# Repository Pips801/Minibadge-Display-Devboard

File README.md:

# Minibadge Display Devboard
A small PCB that allows you to create your own Minibadge displays!

This board provides everything your custom Minibadge display will need, including LiPo battery charging/use and USB-C power. It can be attached board-to-board with your own PCB designs, or it can be wired up using push-in WAGO wire terminals to your existing displays.

## Datasheets
* Voltage regulator - TLV62585RWT - https://www.ti.com/lit/ds/symlink/tlv62585.pdf
* Battery management system - BQ21040 - https://www.ti.com/lit/ds/symlink/bq21040.pdf
* Clock generator - 74HC4060 - https://assets.nexperia.com/documents/data-sheet/74HC_HCT4060.pdf
* Clock driver - DRV8837C - https://www.ti.com/lit/ds/symlink/drv8837c.pdf
* Powepath MUX - TPS2121 - https://www.ti.com/lit/ds/symlink/tps2121.pdf

# Specifications
* Provides your Minibadges battery or USB-C power, 3.3v@3A, CLK, GND, and VBATT.
* Supports LiPo batteries, optionally with NTC temp sensors.
  * 2x LiPo batteries of matching composition, mAh, and charge state can be wired in parallel.
  * 800mA battery charging.
* Features castellated edge-mount pads for direct board to board connections.
* Features WAGO PCB terminal blocks for custom wiring.
* Power switch disconnects minibadges while still powering the battery charging circuit.
* Solderable jumper for disabling temp sensor and selecting CLK speed.

# Limitations
* Input (USB-C): 5V@3A
* Input (Battery): 4.2V@3A
* Battery charging: 4.2V@800mA
* Output (3.3V): 3.3V@3A
* Output (CLK): 3.3V@3A
* Output (SYS): Input voltage@amperage (whichever is higher)
* Max total minibadges: 30-50

# Revisions

R2 Update list
* Better thermal management for voltage regulators under load.
* Updated PMIC ORing power path chip, replacing dual ORing diodes.
* Updated PFET for power on/off switching and system load capacity.
* Better thermal management for PFET under load.
* Improved current flow and reduced waste heat for CLK driver.
* Thicker power traces for 3.3v regulators and Battery.
* Updated silkscreen component markers.
* Updated solder paste for stronger on/off switch mounting.

R3 Update list
* Larger castellated pads for better connection.
* Addition of a second row of pads for pins.
* Swap from 3x LDO regulators to 1x Buck regulator.
* Decreased waste heat and better thermal management.
* Shrunk board height by 2.54mm.
* Added technical limitations on silkscreen.

# Designing a Minibadge display
### Setup
* Import Minibadge footprints and symbols into KiCad.
* Import DevBoard footprint and symbol into KiCad.

### Schematic
* Create schematic with as many minibadges as you want.
* Import the Devboard symbol and wire up CLK, GND, and SYS (VBATT/5V).
* Wire up the minibadges 3.3v lines.

### PCB
* Arrange all of your minibadges.
* Finalize your board shape.
* Place the Devboard on the back of the PCB with the USB port against the edge of your board.
* Wire up your CLK, GND, 3x 3.3v, and SYS (VBATT/5V)

# Assembly
1. Solder the `SPEED` jumper to select the Clock frequency. F for Fast, S for Slow.
2. Solder or attach (through the WAGO) your battery positive and negative leads.
3. If your battery has an NTC temperature wire (third wire, usually white or yellow) connect it to the NTC pad or terminal. Solder the `NTC` jumper to `Y` (Yes NTC)
4. If your battery does not have an NTC temperature wire, solder the `NTC` jumper to the `N` (No NTC) position.
5. Solder or wire up your 3 different 3.3v lines from your display board.
6. Solder or wire up GND, SYS (VBATT/5V), and CLK to the appropriate connections on your display.

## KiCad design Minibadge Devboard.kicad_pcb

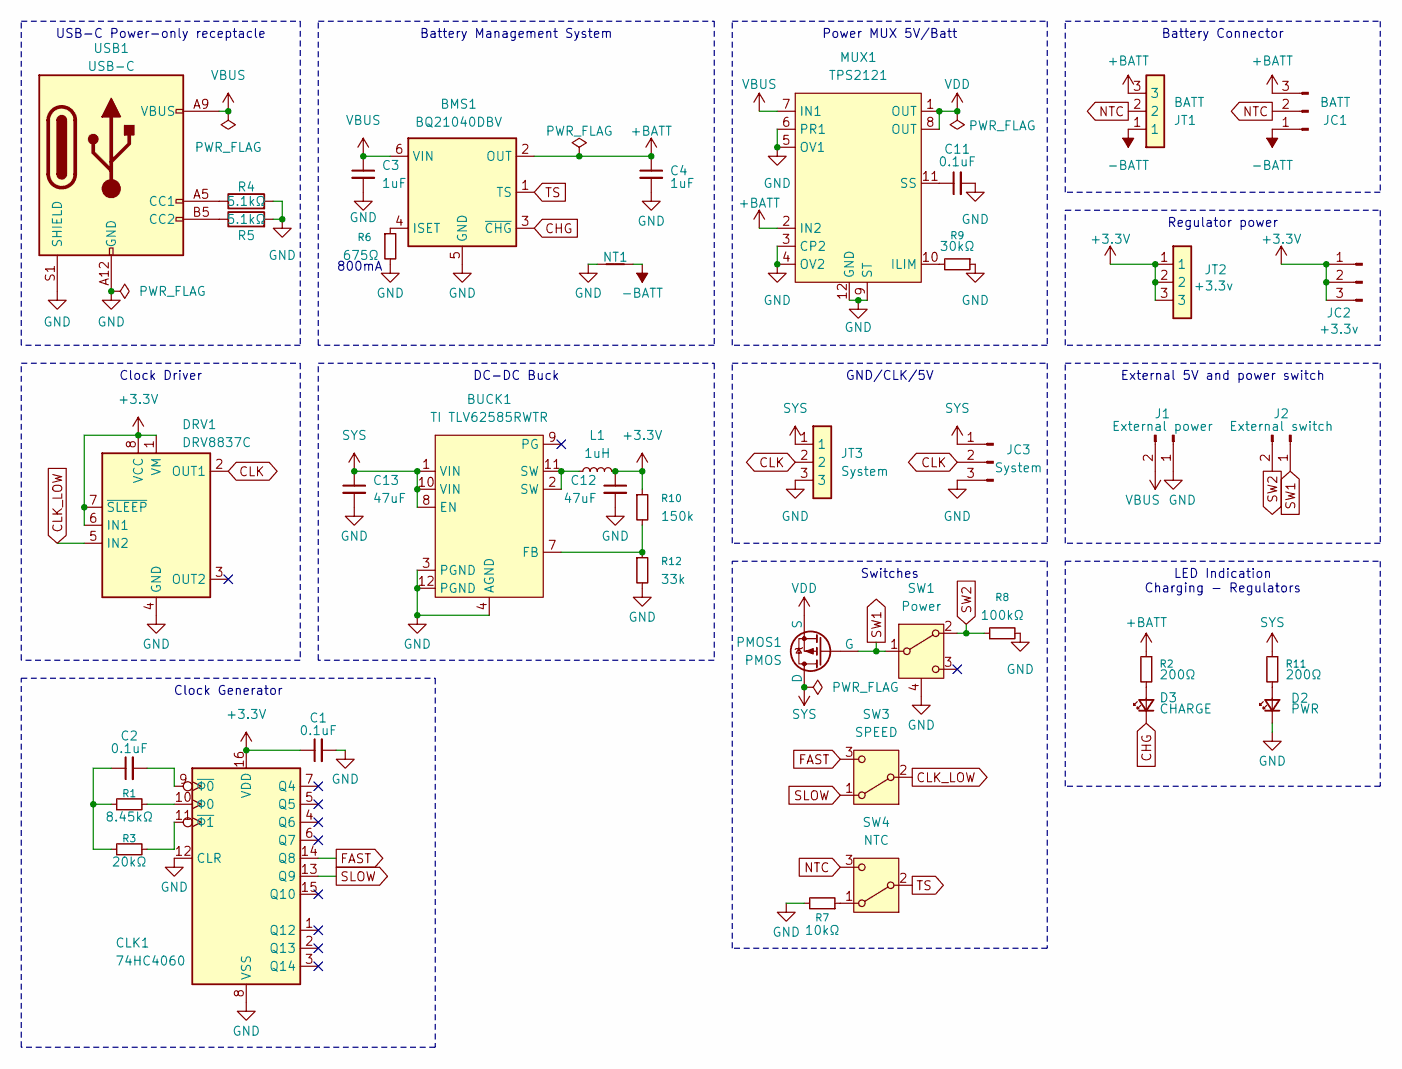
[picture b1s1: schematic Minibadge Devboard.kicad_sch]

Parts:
BMS1: BQ21040DBV; SOT-23-6; LCSC Part # C202311
BUCK1: TI TLV62585RWTR; TLV62585RWTR; LCSC Part # C406872
C1, C2, C11: 0.1uF; C_0603_1608Metric; LCSC Part # C14663
C3, C4: 1uF; C_0603_1608Metric; LCSC Part # C15849
C12, C13: 47uF; C_1206_3216Metric; LCSC Part # C96123
CLK1: 74HC4060; TSSOP-16-1EP_4.4x5mm_P0.65mm; LCSC Part # C354054
D2: PWR; LED_0603_1608Metric; LCSC Part # C2286
D3: CHARGE; LED_0603_1608Metric; LCSC Part # C2286
DRV1: DRV8837C; WSON-8-1EP_2x2mm_P0.5mm_EP0.9x1.6mm; LCSC Part # C191000
J1: External power; Castellated pins 1x02
J2: External switch; Castellated pins 1x02
JC1: BATT; Castellated pins 1x03
JC2: +3.3v; Castellated pins 1x03
JC3: System; Castellated pins 1x03
JT1: BATT; WAGO 2059-303; Manufacturer_Part_Number 2060-453/998-404; LCSC Part # C3309252
JT2: +3.3v; WAGO 2059-303; Manufacturer_Part_Number 2060-453/998-404; LCSC Part # C3309252
JT3: System; WAGO 2059-303; Manufacturer_Part_Number 2060-453/998-404; LCSC Part # C3309252
L1: 1uH; L_KOHERelec_MDA5030; LCSC Part # C2847474
MUX1: TPS2121; Texas_VQFN-HR-12_2x2.5mm_P0.5mm; LCSC Part # C485916
NT1: NetTie_2; NetTie-2_SMD_Pad2.0mm
PMOS1: PMOS; SOT-89-3; LCSC Part # C19272814
R1: 8.45kΩ; R_0603_1608Metric; LCSC Part # C25981
R2, R11: 200Ω; R_0603_1608Metric; LCSC Part # C8218
R3: 20kΩ; R_0603_1608Metric; LCSC Part # C4184
R4, R5: 5.1kΩ; R_0603_1608Metric; LCSC Part # C23186
R6: 675Ω; R_0603_1608Metric; LCSC Part # C23228
R7: 10kΩ; R_0603_1608Metric; LCSC Part # C25804
R8: 100kΩ; R_0603_1608Metric; LCSC Part # C25803
R9: 30kΩ; R_0603_1608Metric; LCSC Part # C22984
R10: 150k; R_0603_1608Metric; LCSC Part # C22807
R12: 33k; R_0603_1608Metric; LCSC Part # C4216
SW1: Power; SW-SMD_SK12D07VG3-T; LCSC Part # C25168821
SW3: SPEED; SolderJumper-3_P1.3mm_Open_RoundedPad1.0x1.5mm_NumberLabels; LCSC Part # C5149822
SW4: NTC; SolderJumper-3_P1.3mm_Open_RoundedPad1.0x1.5mm_NumberLabels; LCSC Part # C5149822
USB1: USB-C; USB_C_Receptacle_HRO_TYPE-C-31-M-17; LCSC Part # C283540

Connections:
+3.3V: C1.1, C12.1, CLK1.16 (VDD), DRV1.1 (VM), DRV1.6 (IN1), DRV1.7 (~SLEEP), DRV1.8 (VCC), JC2.1, JC2.2, JC2.3, JT2.1, JT2.2, JT2.3, L1.2, R10.1
+BATT: BMS1.2 (OUT), C4.1, JC1.3, JT1.3, MUX1.2 (IN2), R2.1
-BATT: JC1.1, JT1.1, NT1.2
CHG: BMS1.3 (~CHG), D3.1 (K)
CLK: DRV1.2 (OUT1), JC3.2, JT3.2
CLK_LOW: DRV1.5 (IN2), SW3.2 (B)
FAST: CLK1.14 (Q8), SW3.3 (C)
GND: BMS1.5 (GND), BUCK1.3 (PGND), BUCK1.4 (AGND), BUCK1.12 (PGND), C1.2, C3.2, C4.2, C11.2, C12.2, C13.2, CLK1.8 (VSS), CLK1.12 (CLR), D2.1 (K), DRV1.4 (GND), DRV1.9 (GND), J1.1, JC3.3, JT3.3, MUX1.3 (CP2), MUX1.4 (OV2), MUX1.5 (OV1), MUX1.6 (PR1), MUX1.9 (ST), MUX1.12 (GND), NT1.1, R4.2, R5.2, R6.2, R7.2, R8.2, R9.1, R12.2, SW1.4, USB1.A12 (GND), USB1.B12 (GND), USB1.S1 (SHIELD)
NTC: JC1.2, JT1.2, SW4.3 (C)
unnamed: BMS1.4 (ISET), R6.1
unnamed: BUCK1.7 (FB), R10.2, R12.1
unnamed: BUCK1.2 (SW), BUCK1.11 (SW), L1.1
unnamed: C2.1, R1.1, R3.1
unnamed: C2.2, CLK1.9 (~Φ0)
unnamed: CLK1.11 (~Φ1), R3.2
unnamed: CLK1.10 (Φ0), R1.2
unnamed: D2.2 (A), R11.2
unnamed: D3.2 (A), R2.2
unnamed: MUX1.10 (ILIM), R9.2
unnamed: C11.1, MUX1.11 (SS)
unnamed: R7.1, SW4.1 (A)
unnamed: R4.1, USB1.A5 (CC1)
unnamed: R5.1, USB1.B5 (CC2)
SLOW: CLK1.13 (Q9), SW3.1 (A)
SW1: J2.1, PMOS1.1 (G), SW1.1 (B)
SW2: J2.2, R8.1, SW1.2 (A)
SYS: BUCK1.1 (VIN), BUCK1.8 (EN), BUCK1.10 (VIN), C13.1, JC3.1, JT3.1, PMOS1.2 (D), R11.1
TS: BMS1.1 (TS), SW4.2 (B)
VBUS: BMS1.6 (VIN), C3.1, J1.2, MUX1.7 (IN1), USB1.A9 (VBUS), USB1.B9 (VBUS)
VDD: MUX1.1 (OUT), MUX1.8 (OUT), PMOS1.3 (S)

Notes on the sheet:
800mA
External 5V and power switch
USB-C Power-only receptacle
DC-DC Buck
Battery Connector
Battery Management System
Power MUX 5V/Batt
LED Indication Charging - Regulators
GND/CLK/5V
Switches
Clock Driver
Clock Generator
Regulator power

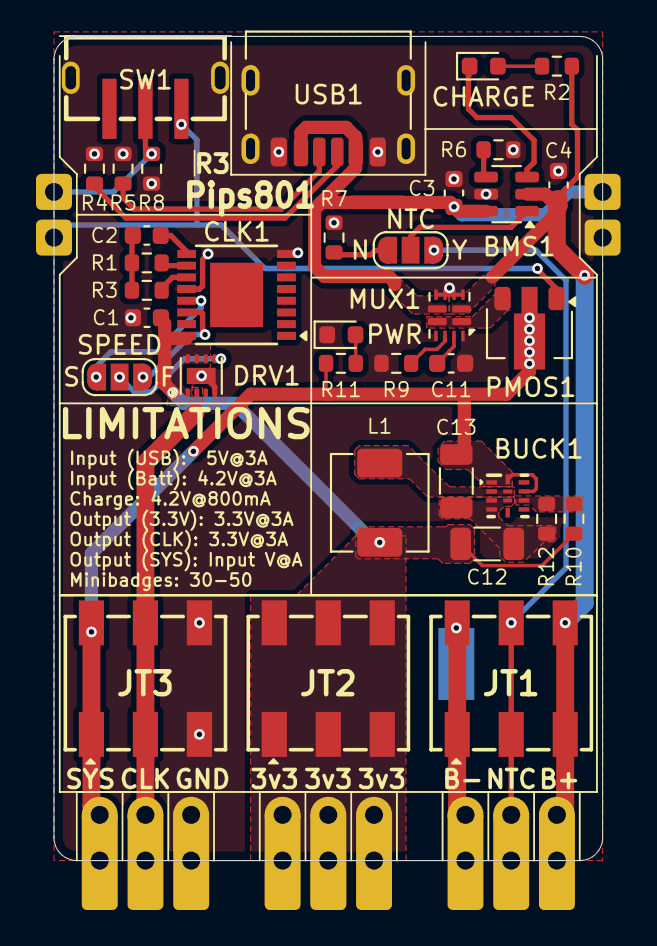
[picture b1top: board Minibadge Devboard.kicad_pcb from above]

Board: 2 copper layers, 30.5 x 45.8 mm, 41 parts (1 on the bottom side), 30 nets.

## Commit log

2025-10-07 add WAGO connector library
2025-10-07 Schematic PDF
2025-10-07 Add WAGO 2059 for smaller footprint
2025-10-07 Add Castellated pins
2025-10-07 layout updates
2025-10-07 update footprints
2025-10-08 Add Footprint and Symbol
2025-10-08 fixes
2025-10-08 Silkscreen fixes and thermal via stitching/anchoring
2025-10-08 Add support for external PSU and Power switch
2025-10-08 update symbol for external power and switch
2025-10-09 BOM updates
2025-10-10 LCSC part numbers
2025-10-11 add 3d render
2025-10-15 Fixes
    * Added text to the footprint to clarify which castellated pin is what
    * Fixed pinout issue with footprint and symbol. SYS and GND were reversed (yikes)
    * Updated schematic symbols and values
    * push updated schematic PDF
2025-10-19 no thermal reliefs
2025-10-19 Copper plane for CLK driver power
2025-10-19 Thermal vias for VREG
2025-10-19 Via tenting
2025-10-19 small fixes
2025-10-19 Swap to TPS2121 for ORing powerpath
2025-10-19 minor fixes
2025-10-19 Upgrade power switching FET
2025-10-19 update positioning and reference designators for silk
2025-10-19 Update schematic drawing
2025-10-19 Board stackup materials
2025-10-19 update STEP file
2025-10-19 Add STL
2025-10-26 Fix symbol
2025-10-30 Extend SW1 pads
2025-10-30 longer pads for SW1
2025-10-31 Fix PMIC copper fills
2025-10-31 Adjust CC traces
2025-10-31 Adjust BATT trace
2025-10-31 Power switch mounting points on GND net
    should hopefully help with thermal transfer to mechanical points for better solder wicking
2025-10-31 Add SYS thermal pour on underside of board for PMOS
    should help PMOS handle heat better
2025-10-31 Trace fixes
2025-10-31 Add solder paste in mechanical hole for SW1 and USB1
2025-10-31 Thicker BATT trace
2025-10-31 Wider solder paste layer on SW1
2025-10-31 update paste layer again
2025-11-01 Add more LEDs to schematic
2025-11-01 Add LCSC part numbers
2025-11-02 Indicators and silkscreen
    * Adjusted all passive component silkscreen thickness.
    * Added labels for batt charging and system power.
    * Added LED for system power.
    * Adjusted positioning for several components.
    * Swapped F and S CLK speed jumper text.
    * Removed CLK indicator (could not fit)
2025-11-02 Update Minibadge Devboard Schematic PDF
2025-11-02 Add 3d model for TPS2121
2025-11-02 Add 3d model for switch
2025-11-02 update traces
2025-11-02 Adjust traces
2025-11-02 Fix power switch mounting hole net
2025-11-03 Calculate ILIM and SS for MUX
    Added LCSC numbers for new parts as well
2025-11-03 Schematic changes
2025-11-03 Update values
2025-11-03 Update PDF for schematics
2025-11-04 upload pictures
2025-11-08 Swap LDO to DC-DC
2025-11-08 Implement/route DC-DC buck
2025-11-08 Update inductor
2025-11-08 Update schematic for R3
2025-11-08 Fix Silkscreen indicators
2025-11-08 fix exclusions
2025-11-08 capacitor spacing for buck
2025-11-09 Updates
    * Fix fast/slow in schematic
    * Fix footprint/schematic issue with WAGO connector
    * Fix update WAGO connector footprint
    * Fix SW1 GND pads
    * Fix via placement on WAGO pads
2025-11-14 Update footprint
